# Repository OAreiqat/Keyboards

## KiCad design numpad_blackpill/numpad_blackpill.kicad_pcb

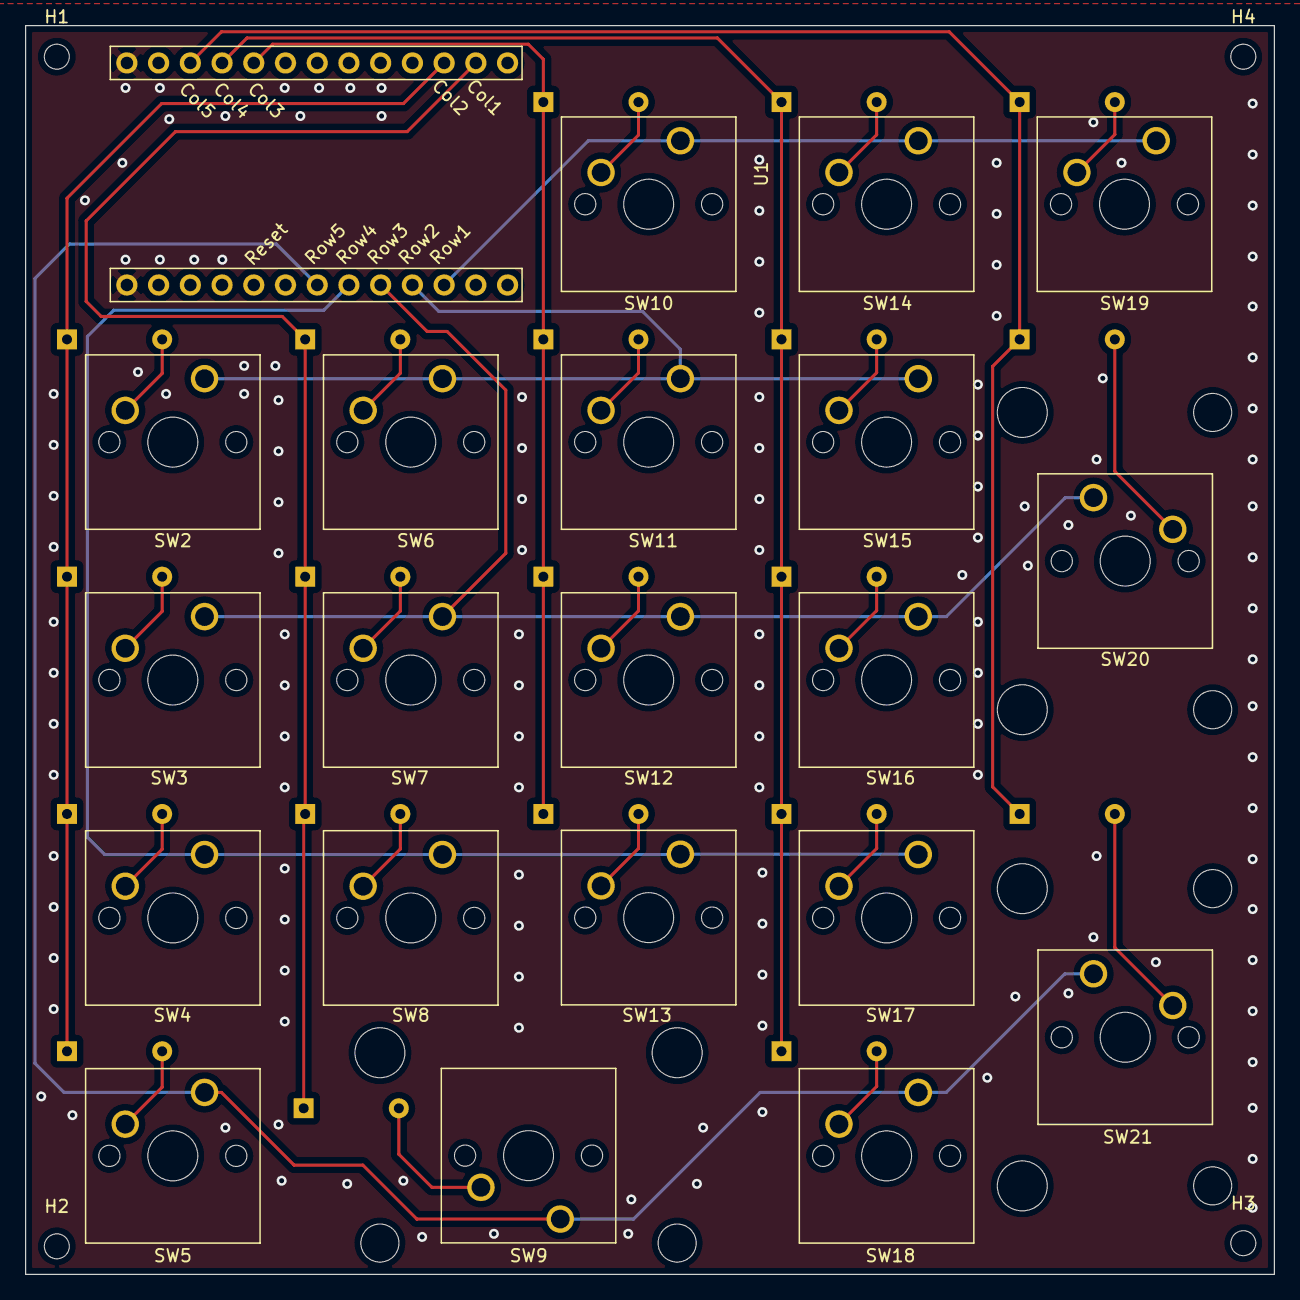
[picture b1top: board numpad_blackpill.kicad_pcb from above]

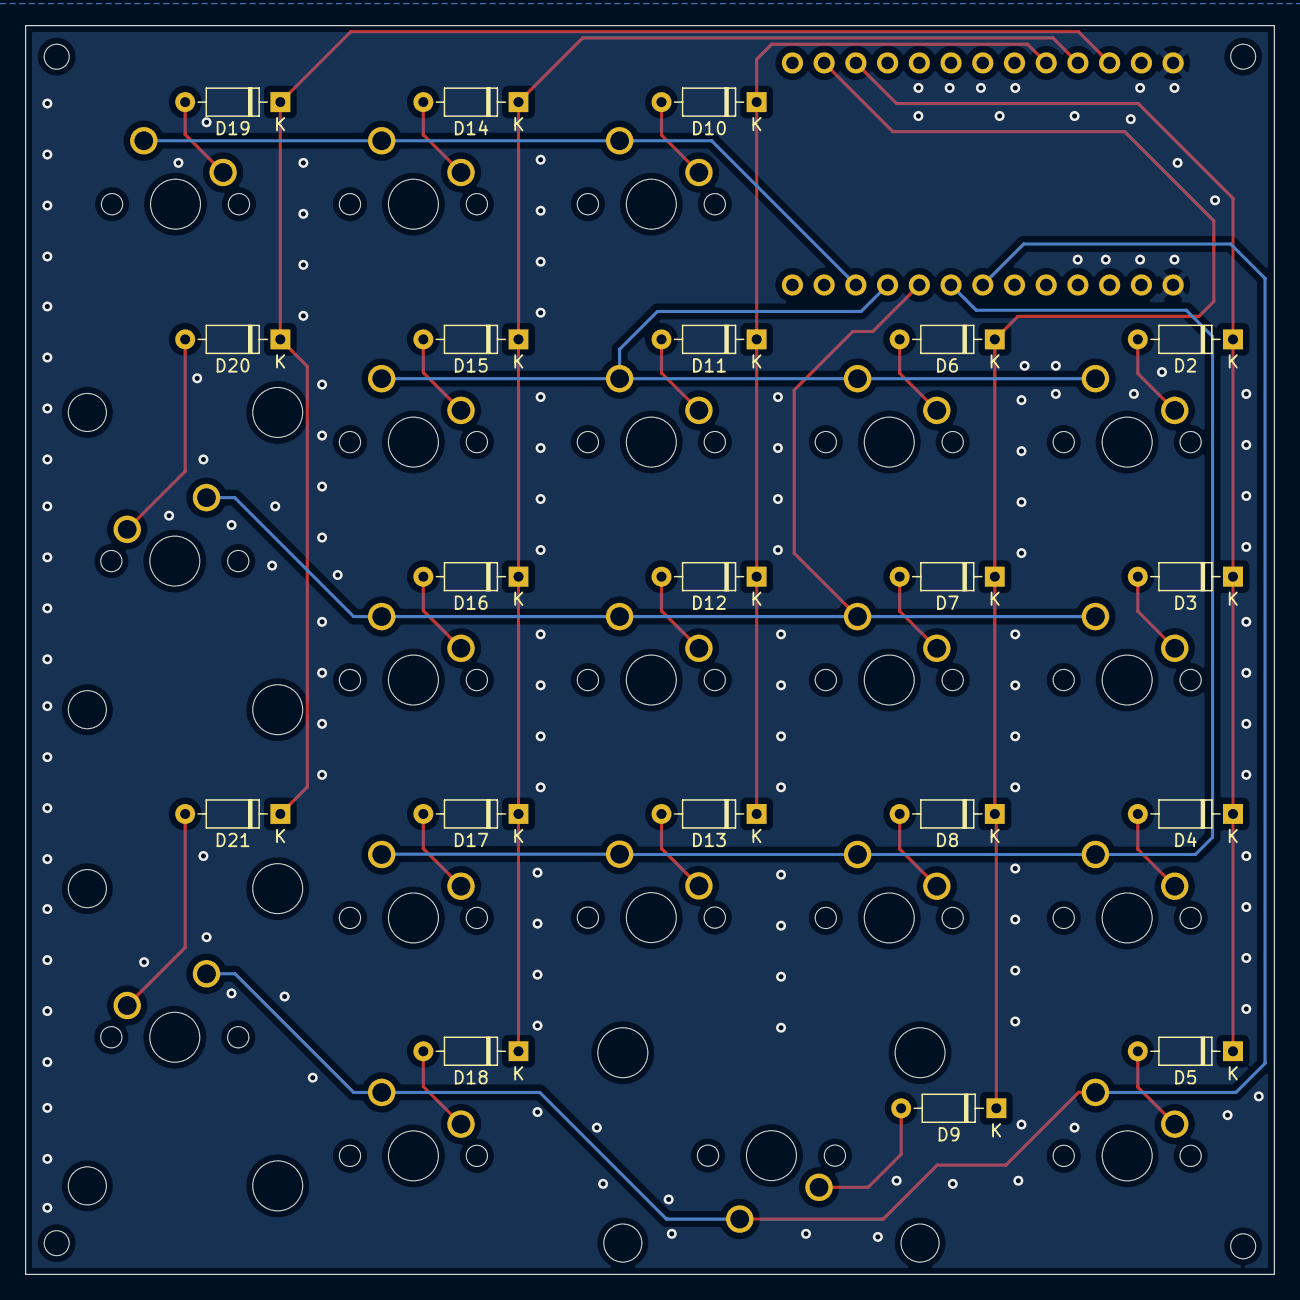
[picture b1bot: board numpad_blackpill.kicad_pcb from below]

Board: 2 copper layers, 100.0 x 100.0 mm, 45 parts (23 on the bottom side), 31 nets.

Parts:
D2, D3, D4, D5, D6, D7, D8, D9, D10, D11, D12, D13, D14, D15, D16, D17, D18, D19, D20, D21: 1N4148; D_DO-35_SOD27_P7.62mm_Horizontal
H1, H2, H3, H4: MountingHole_Pad; MountingHole_2mm
SW2, SW3, SW4, SW5, SW6, SW7, SW8, SW10, SW11, SW12, SW13, SW14, SW15, SW16, SW17, SW18, SW19: SW_Push; SW_Cherry_MX_1.00u_PCB
SW9: SW_Push; SW_Cherry_MX_2.00u_PCB
SW20, SW21: SW_Push; SW_Cherry_MX_2.00u_Vertical_PCB
U1: YAAJ_BlackPill_Part_Like_SWD_Breakout; YAAJ_BlackPill_SWD_3

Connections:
Col1: D2.1 (K), D3.1 (K), D4.1 (K), D5.1 (K), U1.7 (PA10)
Col2: D6.1 (K), D7.1 (K), D8.1 (K), D9.1 (K), U1.6 (PA9)
Col3: D10.1 (K), D11.1 (K), D12.1 (K), D13.1 (K), U1.13 (PB5)
Col4: D14.1 (K), D15.1 (K), D16.1 (K), D17.1 (K), D18.1 (K), U1.14 (PB6)
Col5: D19.1 (K), D20.1 (K), D21.1 (K), U1.15 (PB7)
GND: U1.17 (GND), U1.18 (GND)
unnamed: D2.2 (A), SW2.2
unnamed: D3.2 (A), SW3.2
unnamed: D4.2 (A), SW4.2
unnamed: D5.2 (A), SW5.2
unnamed: D6.2 (A), SW6.2
unnamed: D7.2 (A), SW7.2
unnamed: D8.2 (A), SW8.2
unnamed: D9.2 (A), SW9.2
unnamed: D10.2 (A), SW10.2
unnamed: D11.2 (A), SW11.2
unnamed: D12.2 (A), SW12.2
unnamed: D13.2 (A), SW13.2
unnamed: D14.2 (A), SW14.2
unnamed: D15.2 (A), SW15.2
unnamed: D16.2 (A), SW16.2
unnamed: D17.2 (A), SW17.2
unnamed: D18.2 (A), SW18.2
unnamed: D19.2 (A), SW19.2
unnamed: D20.2 (A), SW20.2
unnamed: D21.2 (A), SW21.2
Row1: SW10.1, SW14.1, SW19.1, U1.28 (PA5)
Row2: SW2.1, SW6.1, SW11.1, SW15.1, U1.27 (PA4)
Row3: SW3.1, SW7.1, SW12.1, SW16.1, SW20.1, U1.26 (PA3)
Row4: SW4.1, SW8.1, SW13.1, SW17.1, U1.25 (PA2)
Row5: SW5.1, SW9.1, SW18.1, SW21.1, U1.24 (PA1)

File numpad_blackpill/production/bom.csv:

Designator,Footprint,Quantity,Value,LCSC Part #
"D10, D11, D12, D13, D14, D15, D16, D17, D18, D19, D2, D20, D21, D3, D4, D5, D6, D7, D8, D9",D_DO-35_SOD27_P7.62mm_Horizontal,20,1N4148,
"H1, H2, H3, H4",MountingHole_2mm,4,MountingHole_Pad,
"SW10, SW11, SW12, SW13, SW14, SW15, SW16, SW17, SW18, SW19, SW2, SW3, SW4, SW5, SW6, SW7, SW8",SW_Cherry_MX_1.00u_PCB,17,SW_Push,
"SW20, SW21",SW_Cherry_MX_2.00u_Vertical_PCB,2,SW_Push,
SW9,SW_Cherry_MX_2.00u_PCB,1,SW_Push,
U1,YAAJ_BlackPill_SWD_3,1,YAAJ_BlackPill_Part_Like_SWD_Breakout,

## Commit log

2022-12-27 Schematic for basic key matrix
2022-12-27 working on numpad PCB
2022-12-30 finished basic numpad with blackpill
2022-12-30 removed encoder from numpad
2023-01-01 Push
